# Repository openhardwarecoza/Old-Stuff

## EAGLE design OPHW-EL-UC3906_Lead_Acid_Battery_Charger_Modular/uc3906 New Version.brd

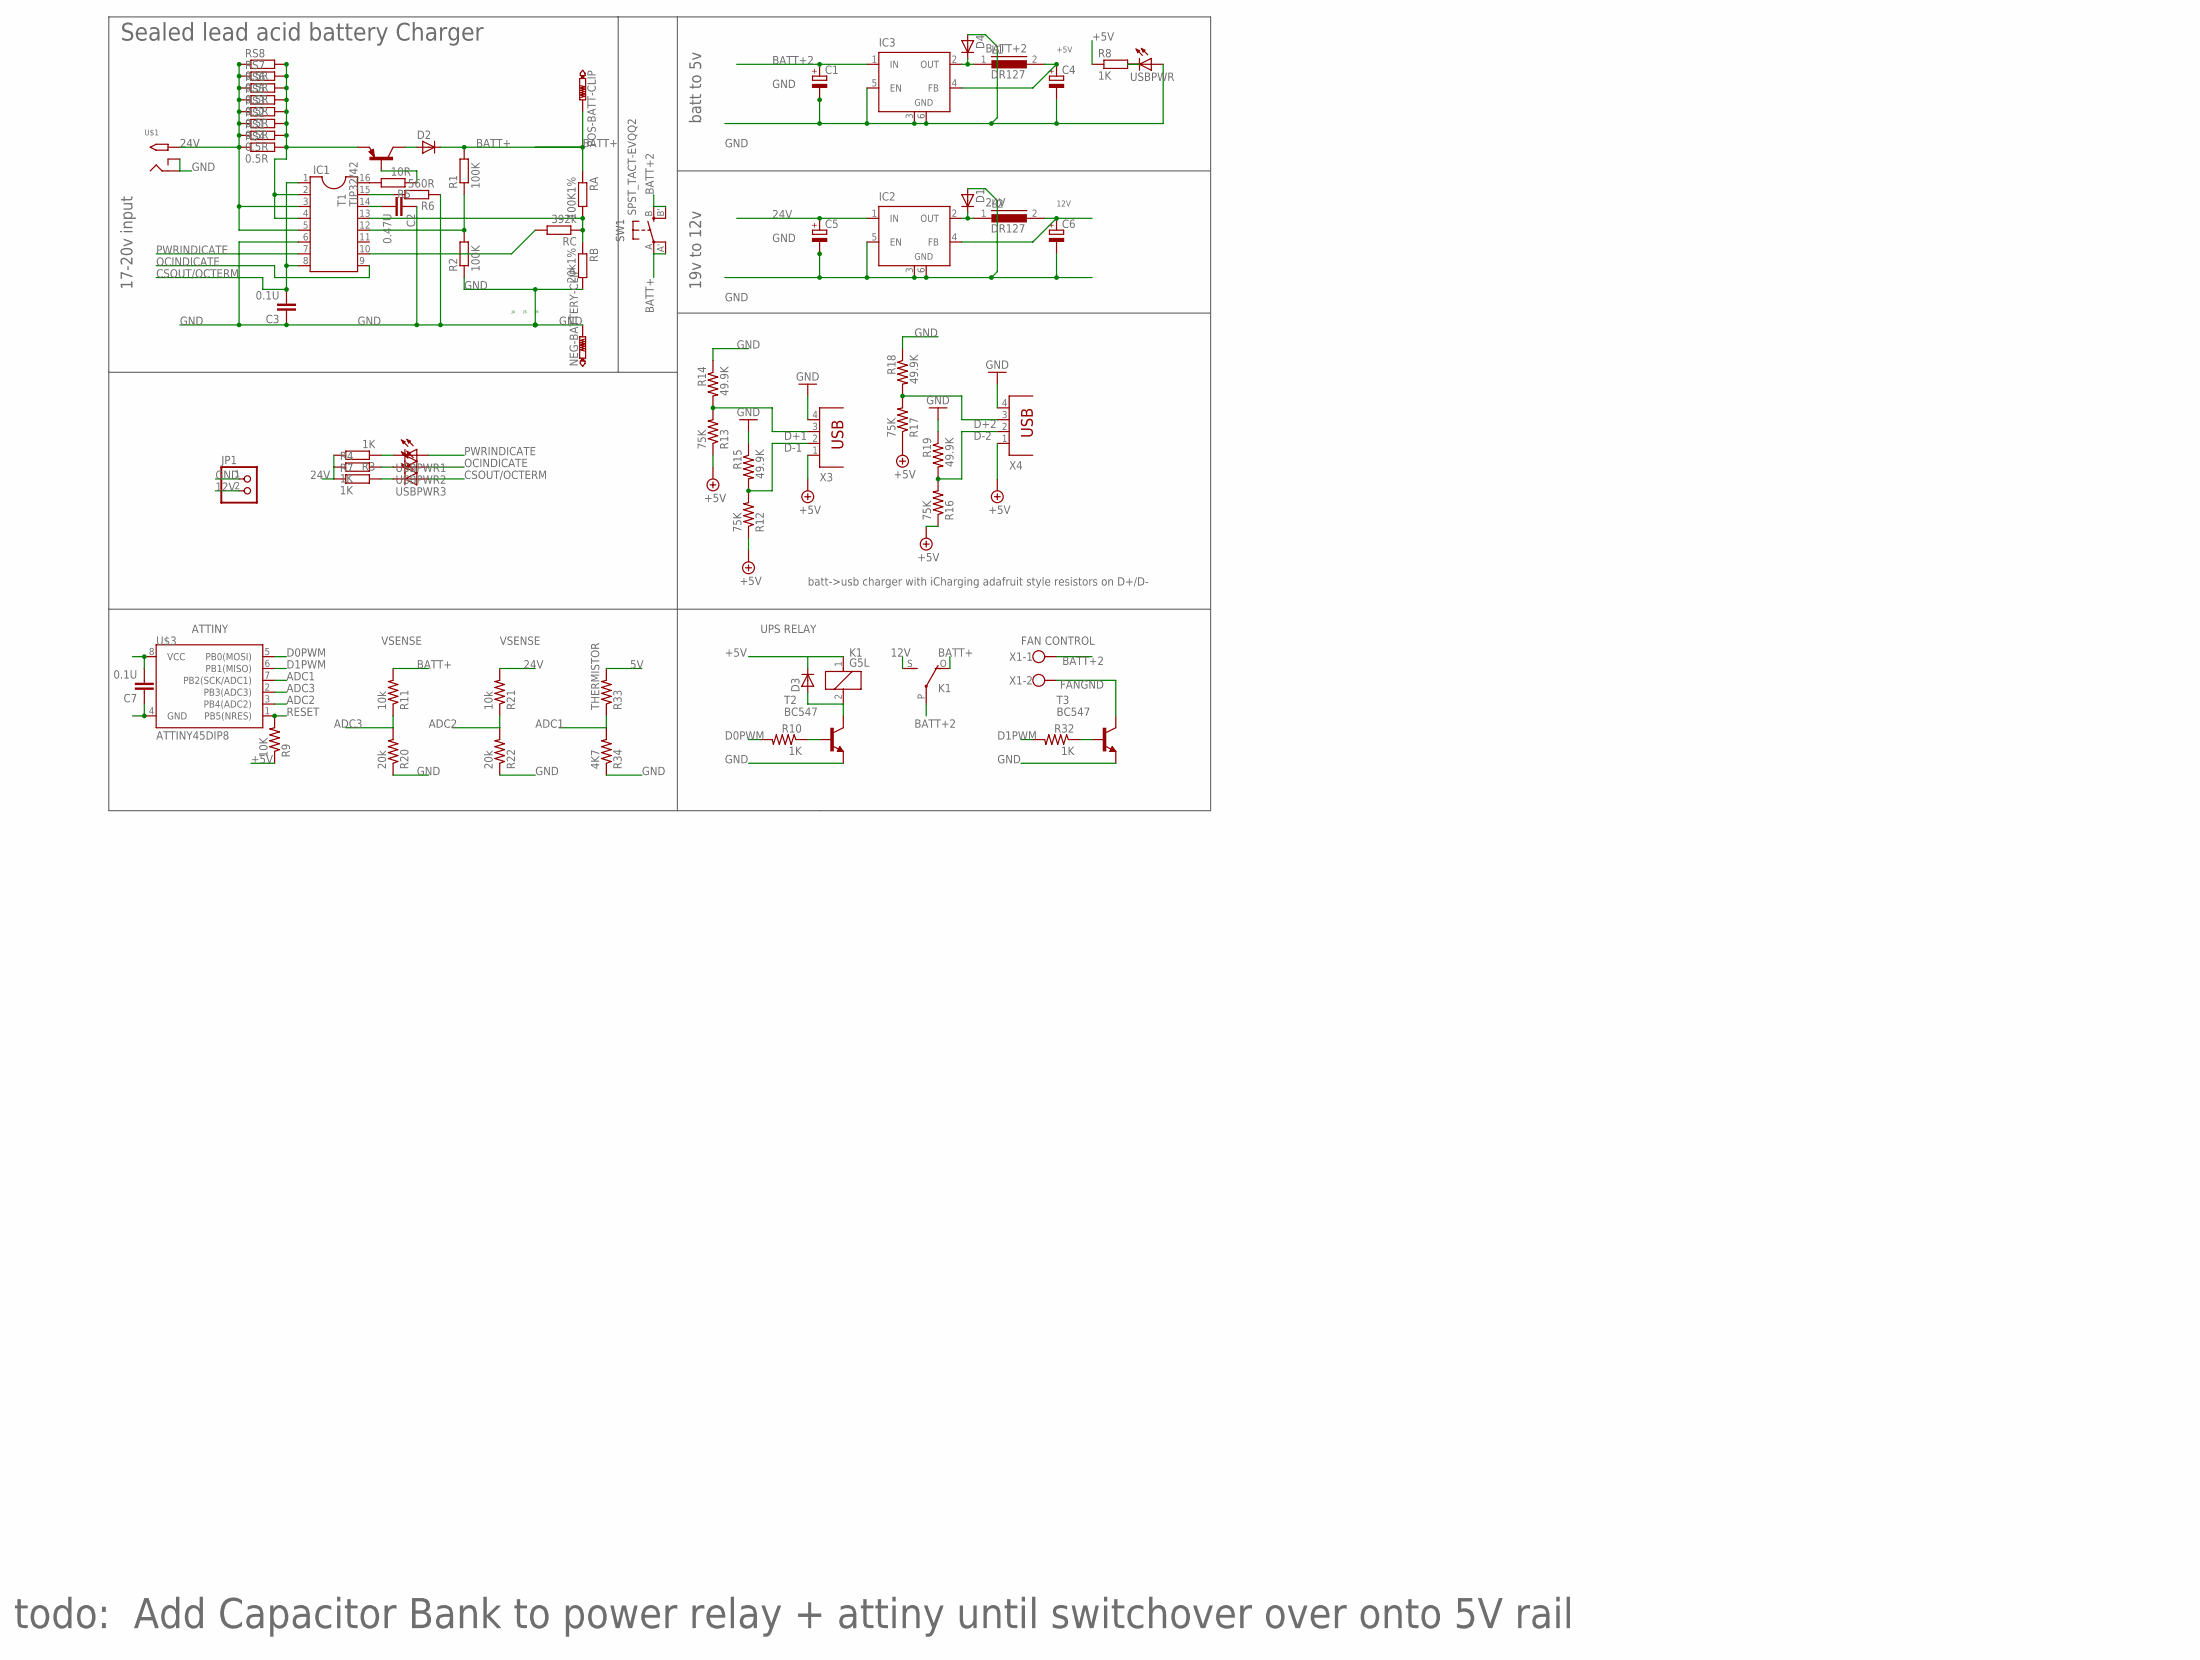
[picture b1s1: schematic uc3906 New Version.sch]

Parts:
C1, C4, C5, C6: CPOL-EUE; PANASONIC_E
C2: 0.47U; C1206
C3, C7: 0.1U; C1206
D1, D4: D-SOD-87; SOD87
D2, D3: D-MLL-41; MELF-MLL41
IC1: DIL16
IC2, IC3: LM2596S; TO263-5
JP1: PINHD-1X2; 1X02
K1: G5L; G5LE
L1, L2: DR127
NEG-BATTERY-CLIP: PTR1PAD1-20Y; P1-20Y
POS-BATT-CLIP: PTR1PAD1-20Y; P1-20Y
R1, R2: 100K; M1206
R3, R4, R7, R8, R10, R32: 1K; M1206
R5: 10R; M1206
R6: 560R; M1206
R9: 10K; M1206
R11, R21: 10k; M1206
R12, R13, R16, R17: 75K; M1206
R14, R15, R18, R19: 49.9K; M1206
R20, R22: 20k; M1206
R33: THERMISTOR; M1206
R34: 4K7; M1206
RA: 100K1%; M1206
RB: 20k1%; M1206
RC: 392k; M1206
RS1, RS2, RS3, RS4, RS5, RS6, RS7, RS8: 0.5R; R2512
SW1: SPST_TACT-EVQQ2; EVQ-Q2
T1: TIP32/42; TO220
T2, T3: BC547; TO92
U$1: 2.1MMJACKTHM; PJ-102A
U$3: ATTINY45DIP8; DIP08
USBPWR: LED3MM
USBPWR1, USBPWR2, USBPWR3: LEDCHIPLED_1206; CHIPLED_1206
X1: W237-102
X3, X4: PN87520

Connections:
5V: R33.2
12V: C6.+, IC2.4 (FB), JP1.2, K1.S, L2.2
24V: C5.+, IC1.3, IC1.5, IC2.1 (IN), R3.2, R4.1, R7.1, R21.2, RS1.1, RS2.1, RS3.1, RS4.1, RS5.1, RS6.1, RS7.1, RS8.1, U$1.TIP
+5V: C4.+, C7.2, D3.1 (C), IC3.4 (FB), K1.1, L1.2, R8.1, R9.1, R12.1, R13.1, R16.1, R17.1, U$3.8 (VCC), X3.1, X4.1
ADC1: R33.1, R34.2, U$3.7 (PB2(SCK/ADC1))
ADC2: R21.1, R22.2, U$3.3 (PB4(ADC2))
ADC3: R11.1, R20.2, U$3.2 (PB3(ADC3))
BATT+: D2.1 (C), K1.O, POS-BATT-CLIP.TP, R1.2, R11.2, RA.1, SW1.A, SW1.A' (P1)
BATT+2: C1.+, IC3.1 (IN), K1.P, SW1.B (S), SW1.B' (S1), X1.1
CHARGEENABLE: IC1.12, R1.1, R2.2
COMPENSATION: C2.2, IC1.14
CSOUT/OCTERM: C3.2, IC1.1, IC1.8, USBPWR3.A
D0PWM: R10.2, U$3.5 (PB0(MOSI))
D1PWM: R32.2, U$3.6 (PB1(MISO))
D+1: R13.2, R14.2, X3.3
D+2: R17.2, R18.2, X4.3
D-1: R12.2, R15.2, X3.2
D-2: R16.2, R19.2, X4.2
DRIVERSINK: IC1.16, R5.2
DRIVERSOURCE: IC1.15, R6.2
FANGND: T3.3 (C), X1.2
GND: C1.-, C2.1, C3.1, C4.-, C5.-, C6.-, C7.1, D1.2 (A), D4.2 (A), IC1.6, IC2.3 (GND), IC2.5 (EN), IC2.6 (GND), IC3.3 (GND), IC3.5 (EN), IC3.6 (GND), JP1.1, NEG-BATTERY-CLIP.TP, R2.1, R6.1, R14.1, R15.1, R18.1, R19.1, R20.1, R22.1, R34.1, RB.2, T2.1 (E), T3.1 (E), U$1.RING, U$1.RING_SW, U$3.4 (GND), USBPWR.A, X3.4, X4.4
IOUT: IC1.2, IC1.4, RS1.2, RS2.2, RS3.2, RS4.2, RS5.2, RS6.2, RS7.2, RS8.2, T1.3 (E)
unnamed: R3.1, USBPWR1.C
unnamed: D1.1 (C), IC2.2 (OUT), L2.1
unnamed: D4.1 (C), IC3.2 (OUT), L1.1
unnamed: R4.2, USBPWR2.C
unnamed: R7.2, USBPWR3.C
unnamed: R8.2, USBPWR.K (C)
unnamed: D3.2 (A), K1.2, T2.3 (C)
unnamed: R10.1, T2.2 (B)
unnamed: R5.1, T1.1 (B)
unnamed: D2.2 (A), T1.2 (C)
unnamed: R32.1, T3.2 (B)
OCINDICATE: IC1.9, USBPWR2.A
PWRINDICATE: IC1.7, USBPWR1.A
RESET: R9.2, U$3.1 (PB5(NRES))
STATELEVELCONTROL: IC1.10, RC.2
VSENSE: IC1.13, RA.2, RB.1, RC.1

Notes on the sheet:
batt->usb charger with iCharging adafruit style resistors on D+/D-
Sealed lead acid battery Charger
19v to 12v
batt to 5v
17-20v input
todo: Add Capacitor Bank to power relay + attiny until switchover over onto 5V rail
FAN CONTROL
UPS RELAY
VSENSE
ATTINY

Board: 2 copper layers, 69 parts (2 on the bottom side), 38 nets, no tracks yet.

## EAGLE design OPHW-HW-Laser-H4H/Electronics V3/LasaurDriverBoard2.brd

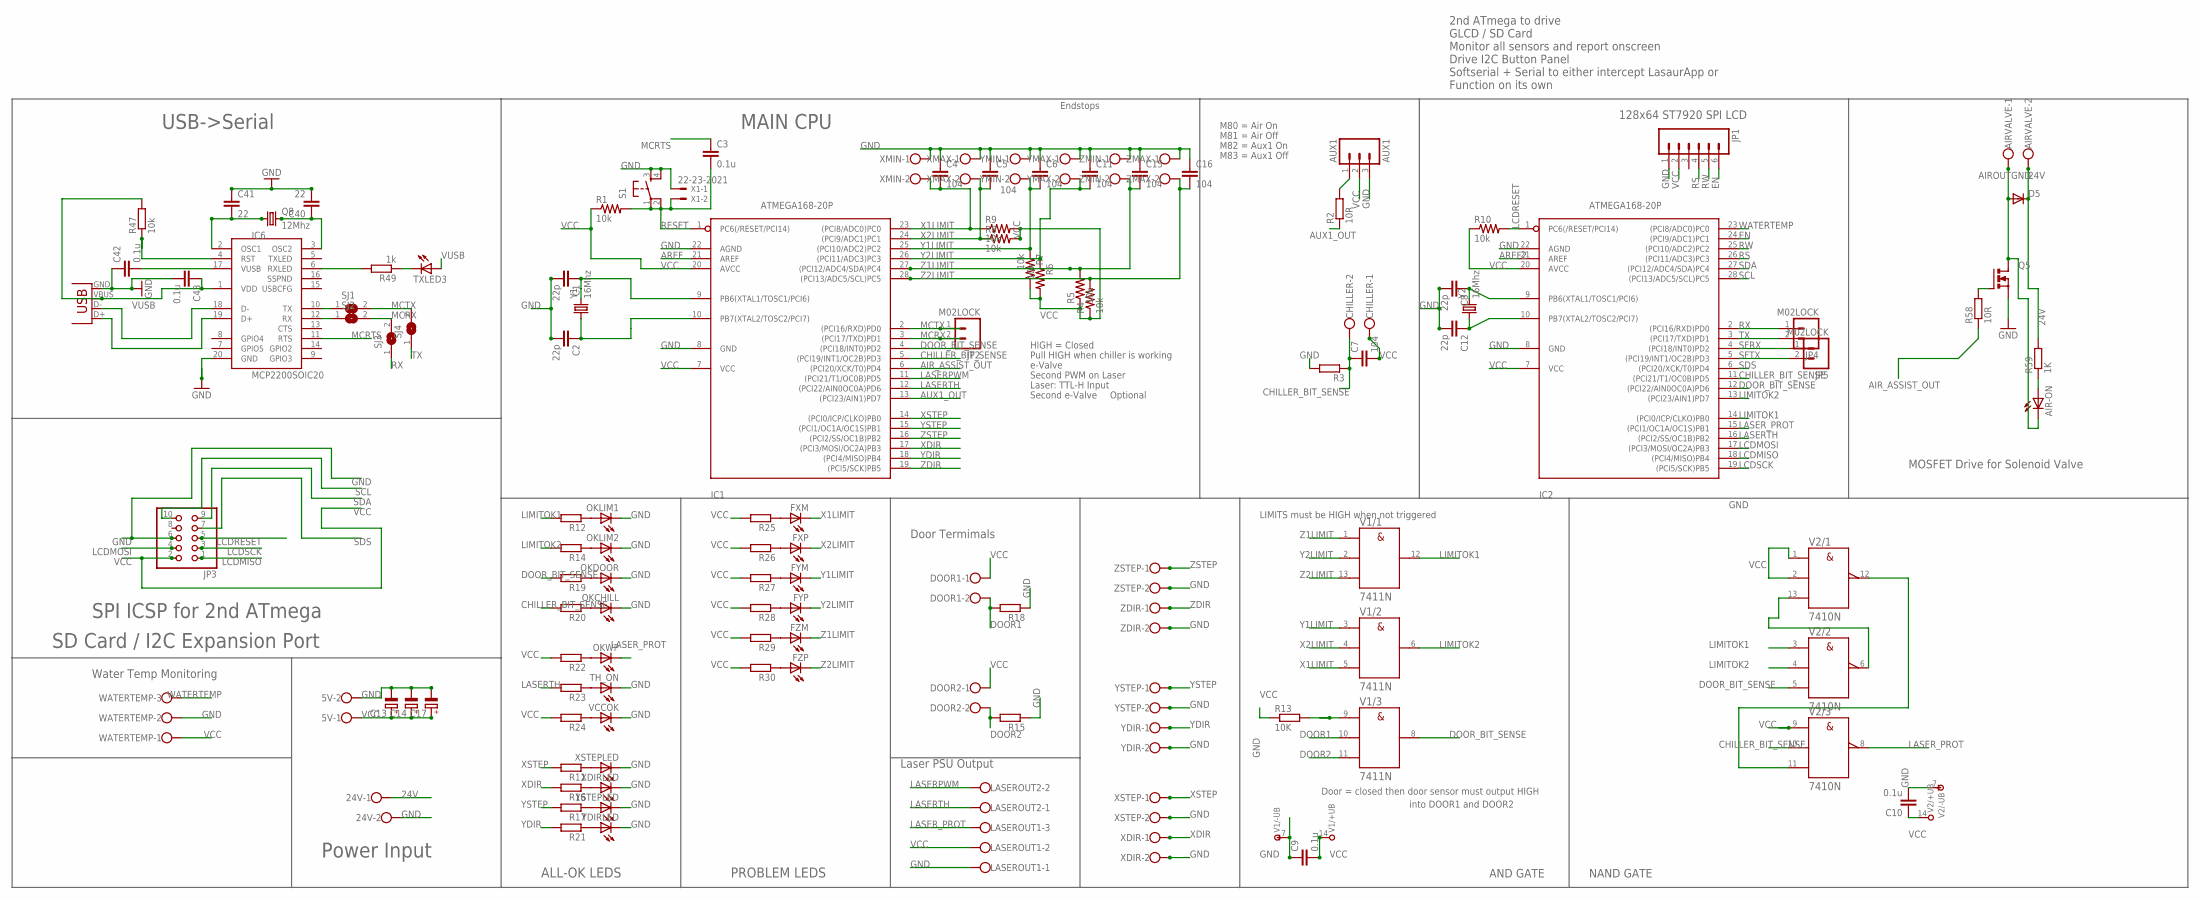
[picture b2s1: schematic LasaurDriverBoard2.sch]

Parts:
5V, 24V: W237-102
AIR-ON: LED3MM
AIRVALVE: W237-102
AUX1: AUX1; MOLEX-1X3
C1, C2, C8, C12: 22p; 1206
C3, C9, C10, C42, C43: 0.1u; 1206
C4, C6, C7, C11, C15, C16: 104; C1206
C5: C-EUC1206; C1206
C13, C14, C17: CPOL-EUB; PANASONIC_B
C40, C41: 22; 1206
CHILLER: W237-102
D5: DIODESMA-ALT; SMA-DIODE_ALT
DOOR1, DOOR2: W237-102
FXM: LED3MM
FXP: LED3MM
FYM: LED3MM
FYP: LED3MM
FZM: LED3MM
FZP: LED3MM
IC1, IC2: ATMEGA168-20P; DIL28-3
IC6: MCP2200SOIC20; SOIC20
JP1: M06LOCK; 1X06_LOCK
JP2, JP4, JP5: M02LOCK; 1X02_LOCK
JP3: PINHD-2X5; 2X05
LASEROUT1: W237-103
LASEROUT2: W237-102
OKCHILL: LED3MM
OKDOOR: LED3MM
OKLIM1, OKLIM2: LED3MM
OKWP: LED3MM
Q5: PMOSFET_NTO220BV; TO220BV
Q8: 12Mhz; HC49UP
R1, R4, R5, R6, R7, R8, R9, R10, R47: 10k; M1206
R2, R58: 10R; M1206
R3, R11, R12, R14, R15, R16, R17, R18, R19, R20, R21, R22, R23, R24, R25, R26, R27, R28, R29, R30: R-EU_M1206; M1206
R13: 10K; M1206
R49: 1k; M1206
R59: 1K; M1206
S1: TAC_SWITCHPTH; TACTILE-PTH
SJ1, SJ2, SJ3, SJ4: SJ
TH_ON: LED3MM
TXLED3: LEDSMT1206; 1206
V1: 7411N; DIL14
V2: 7410N; DIL14
VCCOK: LED3MM
WATERTEMP: W237-103
X1: 22-23-2021
X3: USB-SMD-NS; USB-MINIB-NOSTOP
XDIR: W237-102
XDIRLED: LED3MM
XMAX: W237-102
XMIN: W237-102
XSTEP: W237-102
XSTEPLED: LED3MM
Y1, Y2: 16Mhz; HC49UP
YDIR: W237-102
YDIRLED: LED3MM
YMAX: W237-102
YMIN: 104; W237-102
YSTEP: W237-102
YSTEPLED: LED3MM
ZDIR: W237-102
ZMAX: W237-102
ZMIN: W237-102
ZSTEP: W237-102

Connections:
24V: 24V.1, AIRVALVE.2, D5.C, R59.2
AIROUTGND: AIR-ON.K (C), AIRVALVE.1, D5.A, Q5.D
AIR_ASSIST_OUT: IC1.6 ((PCI20/XCK/T0)PD4), R58.1
AREF: IC1.21 (AREF)
AREF2: IC2.21 (AREF)
AUX1_OUT: IC1.13 ((PCI23/AIN1)PD7), R2.1
CHILLER_BIT_SENSE: C7.1, CHILLER.2, IC1.5 ((PCI19/INT1/OC2B)PD3), IC2.11 ((PCI21/T1/OC0B)PD5), R3.1, R20.2, V2.10 (B)
DOOR1: DOOR1.2, R18.2, V1.10 (B)
DOOR2: DOOR2.2, R15.2, V1.11 (C)
DOOR_BIT_SENSE: IC1.4 ((PCI18/INT0)PD2), IC2.12 ((PCI22/AIN0OC0A)PD6), R19.2, V1.8 (Y), V2.5 (C)
EN: IC2.24 ((PCI9/ADC1)PC1), JP1.6
GND: 5V.2, 24V.2, AUX1.3, C1.2, C2.2, C4.1, C5.1, C6.1, C8.2, C9.1, C10.2, C11.1, C12.2, C13.-, C14.-, C15.1, C16.1, C17.-, C40.2, C41.1, C42.1, C43.2, IC1.8 (GND), IC1.22 (AGND), IC2.8 (GND), IC2.22 (AGND), IC6.20 (GND), JP1.1, JP3.6, LASEROUT1.1, OKCHILL.K (C), OKDOOR.K (C), OKLIM1.K (C), OKLIM2.K (C), Q5.S, R3.2, R15.1, R18.1, S1.3, S1.4, TH_ON.K (C), V1.7 (-UB), V2.7 (-UB), VCCOK.K (C), WATERTEMP.2, X1.1, X3.GND, XDIR.2, XDIRLED.K (C), XMAX.1, XMIN.1, XSTEP.2, XSTEPLED.K (C), YDIR.2, YDIRLED.K (C), YMAX.1, YMIN.1, YSTEP.2, YSTEPLED.K (C), ZDIR.2, ZMAX.1, ZMIN.1, ZSTEP.2
LASERPWM: IC1.11 ((PCI21/T1/OC0B)PD5), LASEROUT2.2
LASERTH: IC1.12 ((PCI22/AIN0OC0A)PD6), IC2.16 ((PCI2/SS/OC1B)PB2), LASEROUT2.1, R23.2
LASER_PROT: IC2.15 ((PCI1/OC1A/OC1S)PB1), LASEROUT1.3, OKWP.K (C), V2.8 (Y)
LCDMISO: IC2.18 ((PCI4/MISO)PB4), JP3.1
LCDMOSI: IC2.17 ((PCI3/MOSI/OC2A)PB3), JP3.4
LCDRESET: IC2.1 (PC6(/RESET/PCI14)), JP3.5, R10.2
LCDSCK: IC2.19 ((PCI5/SCK)PB5), JP3.3
LIMITOK1: IC2.14 ((PCI0/ICP/CLKO)PB0), R12.2, V1.12 (Y), V2.3 (A)
LIMITOK2: IC2.13 ((PCI23/AIN1)PD7), R14.2, V1.6 (Y), V2.4 (B)
MCRTS: C3.1, IC6.11 (RTS)
MCRX: IC1.3 ((PCI17/TXD)PD1), JP2.2, SJ2.2, SJ3.2
MCRXPRE: IC6.12 (RX), SJ2.1
MCTX: IC1.2 ((PCI16/RXD)PD0), JP2.1, SJ1.2, SJ4.2
MXTCPRE: IC6.10 (TX), SJ1.1
unnamed: R11.1, XSTEPLED.A
unnamed: R16.1, XDIRLED.A
unnamed: AUX1.1, R2.2
unnamed: V2.6 (Y), V2.13 (C)
unnamed: OKLIM1.A, R12.1
unnamed: R17.1, YSTEPLED.A
unnamed: R21.1, YDIRLED.A
unnamed: R13.2, V1.9 (A)
unnamed: OKLIM2.A, R14.1
unnamed: OKDOOR.A, R19.1
unnamed: OKCHILL.A, R20.1
unnamed: OKWP.A, R22.1
unnamed: R23.1, TH_ON.A
unnamed: R24.1, VCCOK.A
unnamed: FXM.A, R25.1
unnamed: FXP.A, R26.1
unnamed: FYM.A, R27.1
unnamed: FYP.A, R28.1
unnamed: FZM.A, R29.1
unnamed: FZP.A, R30.1
unnamed: Q5.G, R58.2
unnamed: AIR-ON.A, R59.1
unnamed: C41.2, IC6.2 (OSC1), Q8.1
unnamed: C40.1, IC6.3 (OSC2), Q8.2
unnamed: IC6.18 (D-), X3.D-
unnamed: IC6.19 (D+), X3.D+
unnamed: C42.2, IC6.17 (VUSB)
unnamed: IC6.4 (RST), R47.1
unnamed: IC6.6 (RXLED), R49.2
unnamed: R49.1, TXLED3.C
NANDOK: V2.11 (C), V2.12 (Y)
RESET: C3.2, IC1.1 (PC6(/RESET/PCI14)), R1.2, S1.1, S1.2, X1.2
RS: IC2.26 ((PCI11/ADC3)PC3), JP1.4
RW: IC2.25 ((PCI10/ADC2)PC2), JP1.5
RX: IC2.2 ((PCI16/RXD)PD0), JP4.1, SJ3.1
SCL: IC2.28 ((PCI13/ADC5/SCL)PC5), JP3.10
SDA: IC2.27 ((PCI12/ADC4/SDA)PC4), JP3.9
SDS: IC2.6 ((PCI20/XCK/T0)PD4), JP3.7
SFRX: IC2.4 ((PCI18/INT0)PD2), JP5.1
SFTX: IC2.5 ((PCI19/INT1/OC2B)PD3), JP5.2
TX: IC2.3 ((PCI17/TXD)PD1), JP4.2, SJ4.1
VCC: 5V.1, AUX1.2, C7.2, C9.2, C10.1, C13.+, C14.+, C17.+, CHILLER.1, DOOR1.1, DOOR2.1, IC1.7 (VCC), IC1.20 (AVCC), IC2.7 (VCC), IC2.20 (AVCC), JP1.2, JP3.2, LASEROUT1.2, R1.1, R4.1, R5.1, R6.2, R7.2, R8.2, R9.2, R10.1, R13.1, R22.2, R24.2, R25.2, R26.2, R27.2, R28.2, R29.2, R30.2, V1.14 (+UB), V2.1 (A), V2.2 (B), V2.9 (A), V2.14 (+UB), WATERTEMP.1
VUSB: C43.1, IC6.1 (VDD), R47.2, TXLED3.A, X3.VBUS
WATERTEMP: IC2.23 ((PCI8/ADC0)PC0), WATERTEMP.3
X1LIMIT: C4.2, FXM.K (C), IC1.23 ((PCI8/ADC0)PC0), R9.1, V1.5 (C), XMIN.2
X2LIMIT: C5.2, FXP.K (C), IC1.24 ((PCI9/ADC1)PC1), R8.1, V1.4 (B), XMAX.2
XDIR: IC1.17 ((PCI3/MOSI/OC2A)PB3), R16.2, XDIR.1
XSTEP: IC1.14 ((PCI0/ICP/CLKO)PB0), R11.2, XSTEP.1
XTAL1: C1.1, IC1.9 (PB6(XTAL1/TOSC1/PCI6)), Y1.2
XTAL2: C2.1, IC1.10 (PB7(XTAL2/TOSC2/PCI7)), Y1.1
XTAL3: C12.1, IC2.10 (PB7(XTAL2/TOSC2/PCI7)), Y2.1
XTAL4: C8.1, IC2.9 (PB6(XTAL1/TOSC1/PCI6)), Y2.2
Y1LIMIT: C6.2, FYM.K (C), IC1.25 ((PCI10/ADC2)PC2), R7.1, V1.3 (A), YMIN.2
Y2LIMIT: C11.2, FYP.K (C), IC1.26 ((PCI11/ADC3)PC3), R6.1, V1.2 (B), YMAX.2
YDIR: IC1.18 ((PCI4/MISO)PB4), R21.2, YDIR.1
YSTEP: IC1.15 ((PCI1/OC1A/OC1S)PB1), R17.2, YSTEP.1
Z1LIMIT: C15.2, FZM.K (C), IC1.27 ((PCI12/ADC4/SDA)PC4), R5.2, V1.1 (A), ZMIN.2
Z2LIMIT: C16.2, FZP.K (C), IC1.28 ((PCI13/ADC5/SCL)PC5), R4.2, V1.13 (C), ZMAX.2
ZDIR: IC1.19 ((PCI5/SCK)PB5), ZDIR.1
ZSTEP: IC1.16 ((PCI2/SS/OC1B)PB2), ZSTEP.1

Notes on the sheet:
MAIN CPU
M80 = Air On
M81 = Air Off
M82 = Aux1 On
M83 = Aux1 Off
Second PWM on Laser
HIGH = Closed
e-Valve
Second e-Valve
Pull HIGH when chiller is working
Laser: TTL-H Input
Optional
Endstops
Door = closed then door sensor must output HIGH
into DOOR1 and DOOR2
LIMITS must be HIGH when not triggered
PROBLEM LEDS
ALL-OK LEDS
USB->Serial
SPI ICSP for 2nd ATmega
SD Card / I2C Expansion Port
Power Input
Door Termimals
Laser PSU Output
Water Temp Monitoring
AND GATE
NAND GATE
MOSFET Drive for Solenoid Valve
2nd ATmega to drive GLCD / SD Card Monitor all sensors and report onscreen Drive I2C Button Panel Softserial + Serial to either intercept LasaurApp or Function on its own
128x64 ST7920 SPI LCD

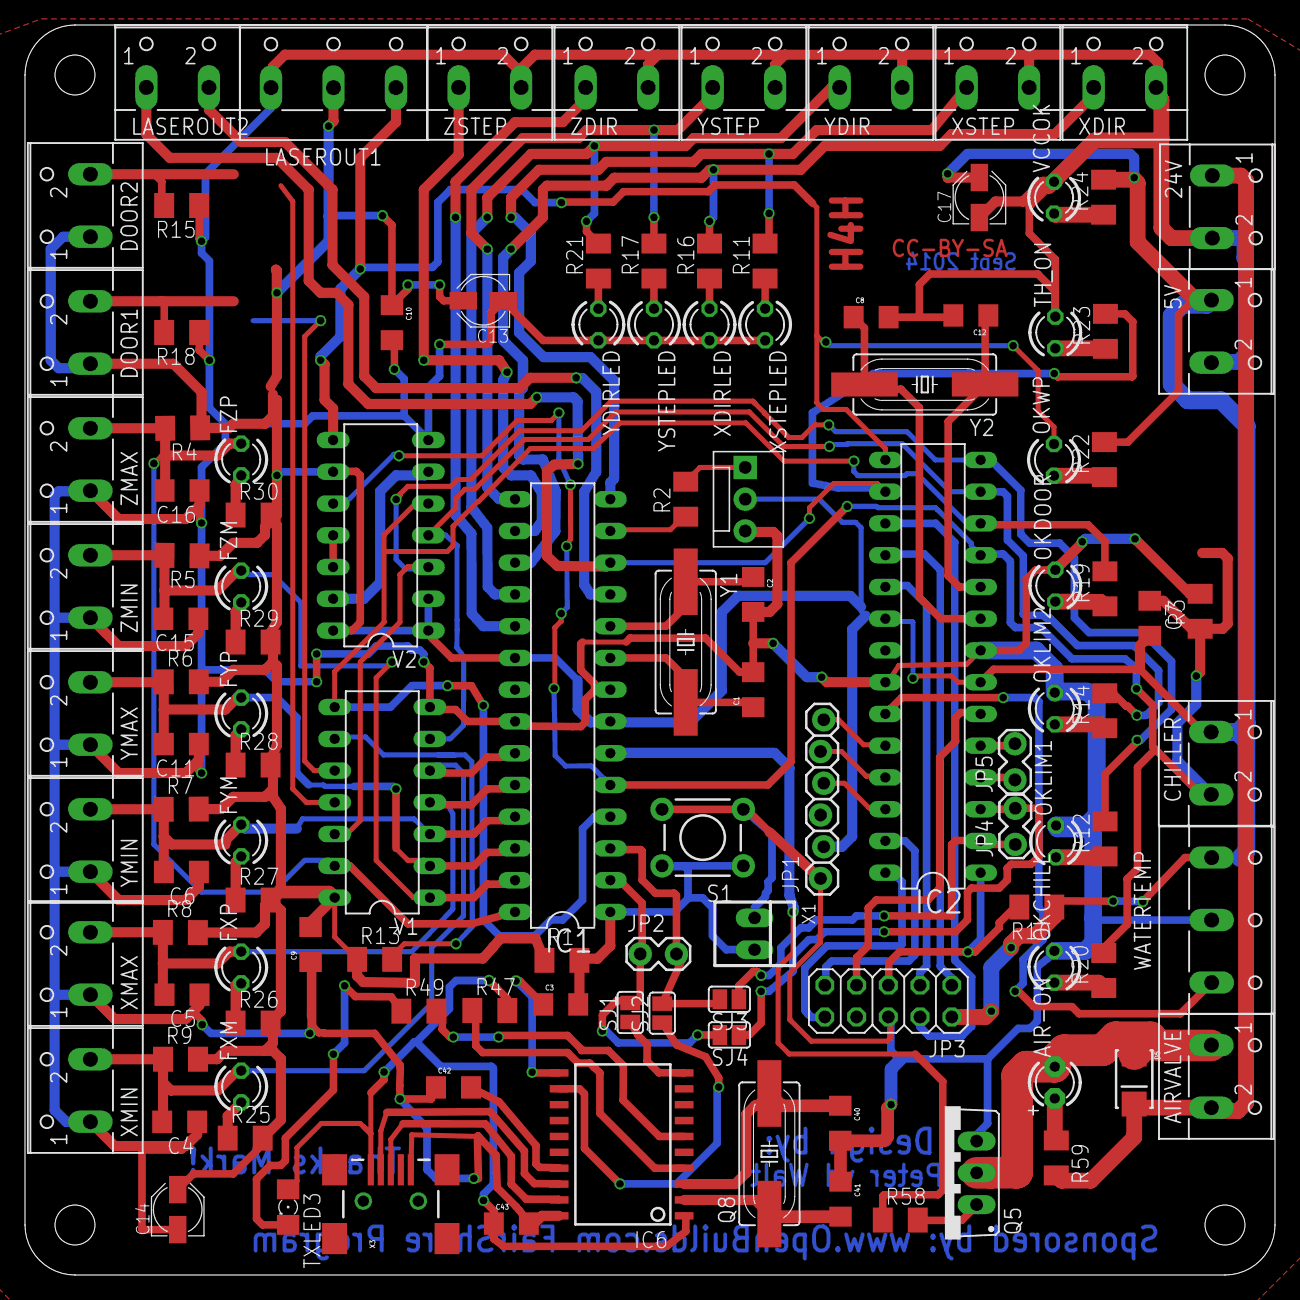
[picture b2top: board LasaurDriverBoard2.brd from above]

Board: 2 copper layers, 100.0 x 100.0 mm, 120 parts (0 on the bottom side), 84 nets.

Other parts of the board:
U$2: DP100100_V1
U$6: LOGO

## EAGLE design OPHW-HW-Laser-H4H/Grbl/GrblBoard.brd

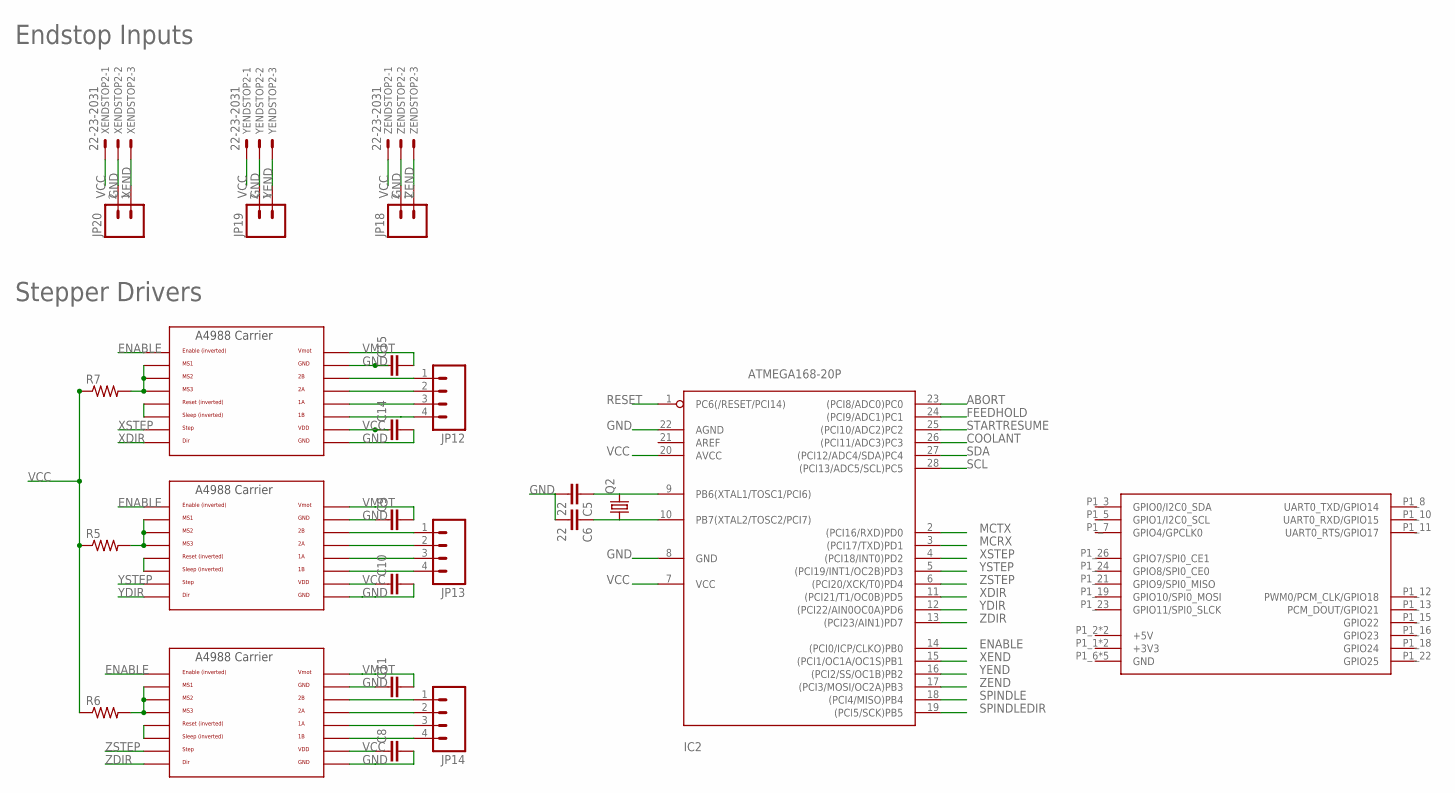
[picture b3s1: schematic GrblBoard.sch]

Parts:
C5, C6: 22; 1206
C8, C9, C10, C11, C14, C15: CAP1206; 1206
IC2: ATMEGA168-20P; DIL28-3
JP12, JP13, JP14: M04SCREW; SCREWTERMINAL-3.5MM-4
JP18, JP19, JP20: M023.5MM; SCREWTERMINAL-3.5MM-2
Q2: CRYSTALHC49UP; HC49UP
R5, R6, R7: RESISTOR1206; 1206
U$1: RPI-B-V1SHIELD; RPI-B-V1-SHIELD
XENDSTOP2: 22-23-2031
XPOL: POLOLU_A4983CARRIER; A4988BREAKOUT
YENDSTOP2: 22-23-2031
YPOL: POLOLU_A4983CARRIER; A4988BREAKOUT
ZENDSTOP2: 22-23-2031
ZPOL: POLOLU_A4983CARRIER; A4988BREAKOUT

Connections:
+3V3: U$1.P1_1 (+3V3), U$1.P1_17 (+3V3)
+5V: U$1.P1_2 (+5V), U$1.P1_4 (+5V)
ABORT: IC2.23 ((PCI8/ADC0)PC0)
COOLANT: IC2.26 ((PCI11/ADC3)PC3)
ENABLE: IC2.14 ((PCI0/ICP/CLKO)PB0), XPOL.EN, YPOL.EN, ZPOL.EN
FEEDHOLD: IC2.24 ((PCI9/ADC1)PC1)
GND: C5.2, C6.2, C8.2, C9.1, C10.2, C11.1, C14.2, C15.1, IC2.8 (GND), IC2.22 (AGND), JP18.2, JP19.2, JP20.2, U$1.P1_6 (GND), U$1.P1_9 (GND), U$1.P1_14 (GND), U$1.P1_20 (GND), U$1.P1_25 (GND), XENDSTOP2.2, XPOL.GND, XPOL.GND@0 (GND), YENDSTOP2.2, YPOL.GND, YPOL.GND@0 (GND), ZENDSTOP2.2, ZPOL.GND, ZPOL.GND@0 (GND)
MCRX: IC2.3 ((PCI17/TXD)PD1)
MCTX: IC2.2 ((PCI16/RXD)PD0)
unnamed: ZPOL.RST, ZPOL.SLP (SLEEP)
unnamed: YPOL.RST, YPOL.SLP (SLEEP)
unnamed: XPOL.RST, XPOL.SLP (SLEEP)
unnamed: R7.2, XPOL.MS1, XPOL.MS2, XPOL.MS3
unnamed: R5.2, YPOL.MS1, YPOL.MS2, YPOL.MS3
unnamed: R6.2, ZPOL.MS1, ZPOL.MS2, ZPOL.MS3
unnamed: JP14.4, ZPOL.1B
unnamed: JP14.3, ZPOL.1A
unnamed: JP14.2, ZPOL.2A
unnamed: JP14.1, ZPOL.2B
unnamed: JP13.1, YPOL.2B
unnamed: JP13.2, YPOL.2A
unnamed: JP13.3, YPOL.1A
unnamed: JP13.4, YPOL.1B
unnamed: JP12.4, XPOL.1B
unnamed: JP12.3, XPOL.1A
unnamed: JP12.2, XPOL.2A
unnamed: JP12.1, XPOL.2B
RESET: IC2.1 (PC6(/RESET/PCI14))
SCL: IC2.28 ((PCI13/ADC5/SCL)PC5)
SDA: IC2.27 ((PCI12/ADC4/SDA)PC4)
SPINDLE: IC2.18 ((PCI4/MISO)PB4)
SPINDLEDIR: IC2.19 ((PCI5/SCK)PB5)
STARTRESUME: IC2.25 ((PCI10/ADC2)PC2)
VCC: C8.1, C10.1, C14.1, IC2.7 (VCC), IC2.20 (AVCC), R5.1, R6.1, R7.1, XENDSTOP2.1, XPOL.VDD, YENDSTOP2.1, YPOL.VDD, ZENDSTOP2.1, ZPOL.VDD
VMOT: C9.2, C11.2, C15.2, XPOL.VMOT, YPOL.VMOT, ZPOL.VMOT
XDIR: IC2.11 ((PCI21/T1/OC0B)PD5), XPOL.DIR
XEND: IC2.15 ((PCI1/OC1A/OC1S)PB1), JP20.1, XENDSTOP2.3
XSTEP: IC2.4 ((PCI18/INT0)PD2), XPOL.STEP
XTAL1: C5.1, IC2.9 (PB6(XTAL1/TOSC1/PCI6)), Q2.2
XTAL2: C6.1, IC2.10 (PB7(XTAL2/TOSC2/PCI7)), Q2.1
YDIR: IC2.12 ((PCI22/AIN0OC0A)PD6), YPOL.DIR
YEND: IC2.16 ((PCI2/SS/OC1B)PB2), JP19.1, YENDSTOP2.3
YSTEP: IC2.5 ((PCI19/INT1/OC2B)PD3), YPOL.STEP
ZDIR: IC2.13 ((PCI23/AIN1)PD7), ZPOL.DIR
ZEND: IC2.17 ((PCI3/MOSI/OC2A)PB3), JP18.1, ZENDSTOP2.3
ZSTEP: IC2.6 ((PCI20/XCK/T0)PD4), ZPOL.STEP

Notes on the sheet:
Endstop Inputs
Stepper Drivers

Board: 2 copper layers, 26 parts (0 on the bottom side), 35 nets, no tracks yet.

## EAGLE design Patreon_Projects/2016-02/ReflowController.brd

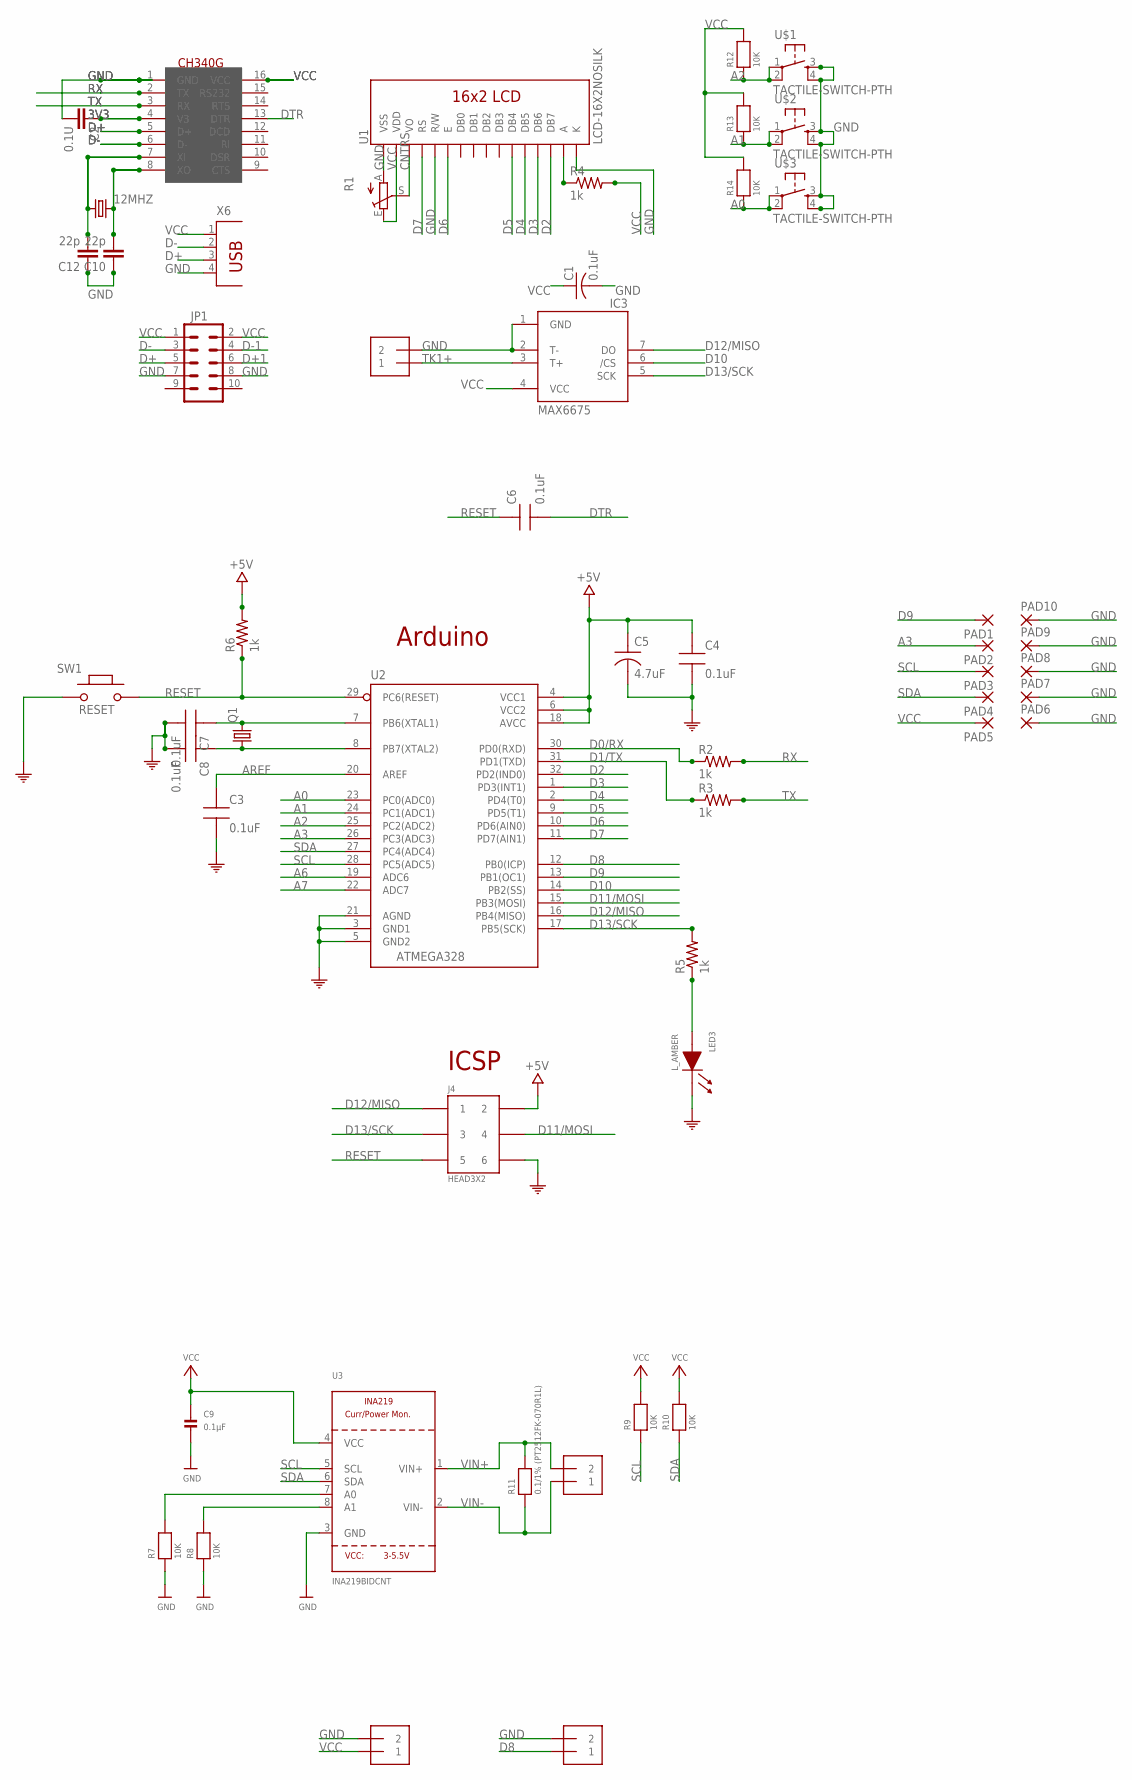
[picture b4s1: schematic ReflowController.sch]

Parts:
12MHZ: CRYSTALHC49UP; HC49UP
C1: 0.1uF; C0805K
C2: 0.1U; C1206
C3, C4, C6, C7, C8: 0.1uF; CAP0805-NP
C5: 4.7uF; TAN-A
C9: 0.1µF; 0805
C10, C12: 22p; C1206
IC3: MAX6675; SO08
J1, J3, J5: TERMBLOCK_1X2-3.5MM; 1X2-3.5MM
J2: 1X2-3.5MM
J4: HEAD3X2
JP1: M05X2SHD_LOCK; 2X5-SHROUDED_LOCK
LED3: L_AMBER; LED0805
PAD1, PAD2, PAD3, PAD4, PAD5, PAD6, PAD7, PAD8, PAD9, PAD10: SMD2; SMD1,27-2,54
Q1: CRYSTALHC49UP; HC49UP
R1: TRIM_EU-CA9V; CA9V
R2, R3, R4, R5, R6: 1k; 1206
R7, R8, R9, R10, R12, R13, R14: 10K; 0805
R11: 0.1/1% (PT2512FK-070R1L); 2512
SW1: RESET; 157SW
U1: LCD-16X2NOSILK; LCD-16X2_NOSILK
U2: ATMEGA328; QFP032
U3: INA219BIDCNT; SOT23-8
U$1, U$2, U$3: TACTILE-SWITCH-PTH; TAC-SWITCH-PTH
U$4: CH340G; SOIC16
X6: PN61729

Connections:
3V3: C2.1, U$4.4 (V3)
A0: R14.1, U2.23 (PC0(ADC0)), U$3.1, U$3.2
A1: R13.1, U2.24 (PC1(ADC1)), U$2.1, U$2.2
A2: R12.1, U2.25 (PC2(ADC2)), U$1.1, U$1.2
A3: PAD2.1, U2.26 (PC3(ADC3))
A6: U2.19 (ADC6)
A7: U2.22 (ADC7)
AREF: C3.1, U2.20 (AREF)
CNTRS: R1.S, U1.3 (VO)
D0/RX: R2.1, U2.30 (PD0(RXD))
D1/TX: R3.1, U2.31 (PD1(TXD))
D2: U1.14 (DB7), U2.32 (PD2(IND0))
D3: U1.13 (DB6), U2.1 (PD3(INT1))
D4: U1.12 (DB5), U2.2 (PD4(T0))
D5: U1.11 (DB4), U2.9 (PD5(T1))
D6: U1.6 (E), U2.10 (PD6(AIN0))
D7: U1.4 (RS), U2.11 (PD7(AIN1))
D8: J3.1, U2.12 (PB0(ICP))
D9: PAD1.1, U2.13 (PB1(OC1))
D10: IC3.6 (/CS), U2.14 (PB2(SS))
D11/MOSI: J4.4, U2.15 (PB3(MOSI))
D12/MISO: IC3.7 (DO), J4.1, U2.16 (PB4(MISO))
D13/SCK: IC3.5 (SCK), J4.3, R5.2, U2.17 (PB5(SCK))
D+: JP1.5, U$4.5 (D+), X6.3
D+1: JP1.6
D-: JP1.3, U$4.6 (D-), X6.2
D-1: JP1.4
DTR: C6.2, U$4.13 (DTR)
GND: C1.2, C2.2, C3.2, C4.2, C5.2, C7.2, C8.2, C9.2, C10.1, C12.1, IC3.1 (GND), IC3.2 (T-), J2.2, J3.2, J4.6, J5.2, JP1.7, JP1.8, LED3.1 (CA), PAD6.1, PAD7.1, PAD8.1, PAD9.1, PAD10.1, R1.A, R7.1, R8.1, SW1.1, U1.1 (VSS), U1.5 (R/W), U1.16 (K), U2.3 (GND1), U2.5 (GND2), U2.21 (AGND), U3.3 (GND), U$1.3, U$1.4, U$2.3, U$2.4, U$3.3, U$3.4, U$4.1 (GND), X6.4
unnamed: C8.1, Q1.1, U2.8 (PB7(XTAL2))
unnamed: C7.1, Q1.2, U2.7 (PB6(XTAL1))
unnamed: R8.2, U3.8 (A1)
unnamed: R7.2, U3.7 (A0)
unnamed: LED3.2 (AN), R5.1
unnamed: R4.1, U1.15 (A)
unnamed: 12MHZ.1, C12.2, U$4.7 (XI)
unnamed: 12MHZ.2, C10.2, U$4.8 (XO)
RESET: C6.1, J4.5, R6.1, SW1.2, U2.29 (PC6(RESET))
RX: R2.2, U$4.2 (TX)
SCL: PAD3.1, R9.1, U2.28 (PC5(ADC5)), U3.5 (SCL)
SDA: PAD4.1, R10.1, U2.27 (PC4(ADC4)), U3.6 (SDA)
TK1+: IC3.3 (T+), J2.1
TX: R3.2, U$4.3 (RX)
VCC: C1.1, C4.1, C5.1, C9.1, IC3.4 (VCC), J4.2, J5.1, JP1.1, JP1.2, PAD5.1, R1.E, R4.2, R6.2, R9.2, R10.2, R12.2, R13.2, R14.2, U1.2 (VDD), U2.4 (VCC1), U2.6 (VCC2), U2.18 (AVCC), U3.4 (VCC), U$4.16 (VCC), X6.1
VIN+: J1.2, R11.2, U3.1 (VIN+)
VIN-: J1.1, R11.1, U3.2 (VIN-)

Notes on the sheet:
Arduino
ICSP

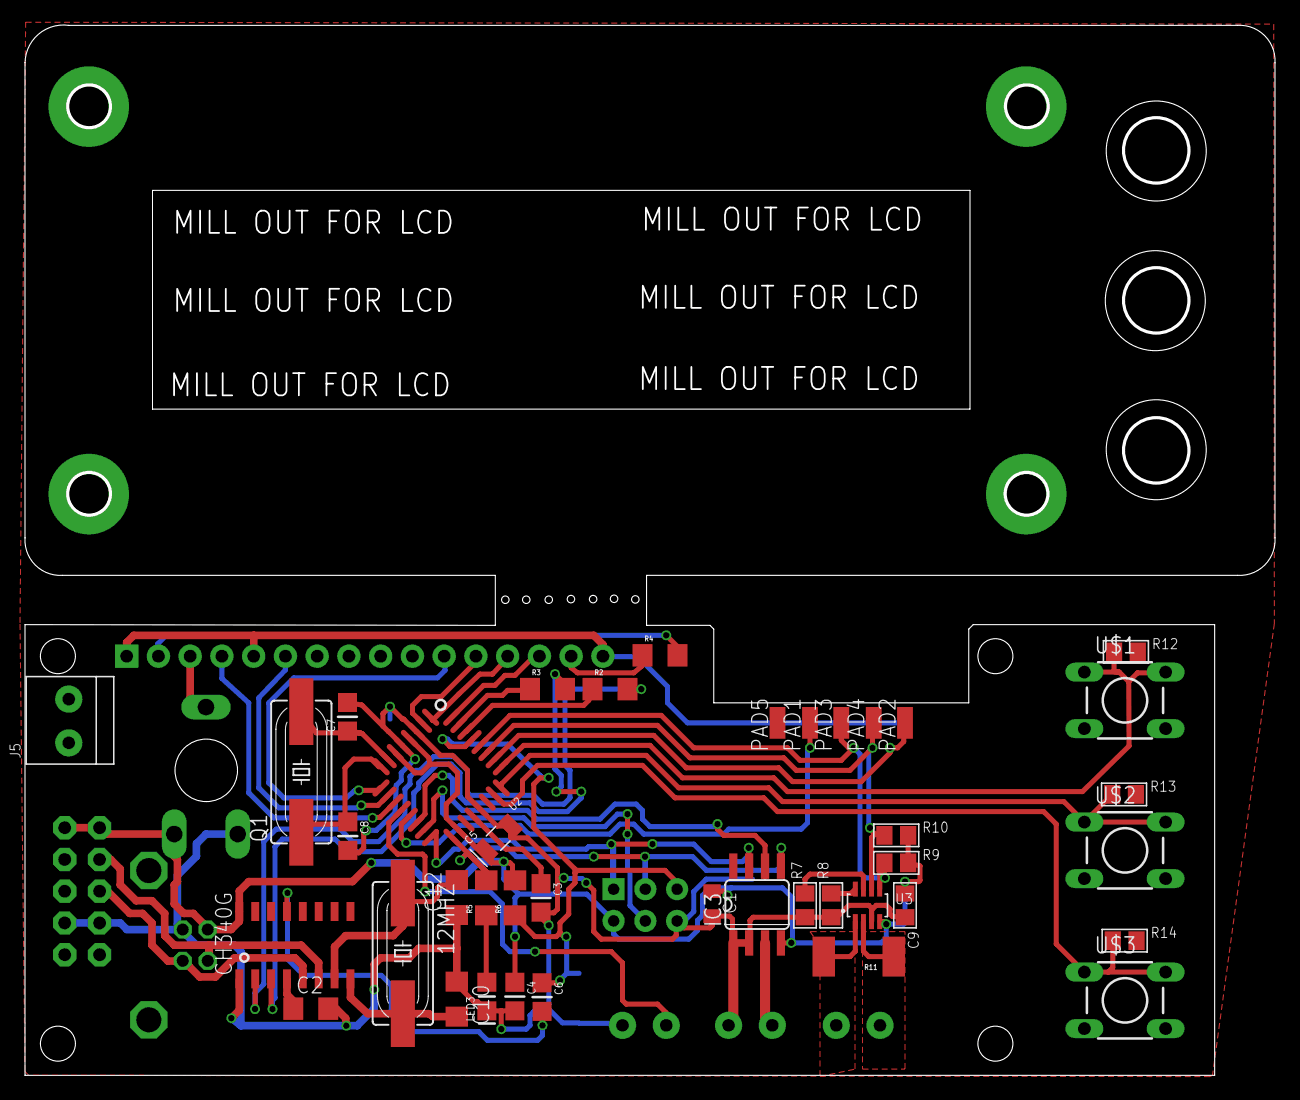
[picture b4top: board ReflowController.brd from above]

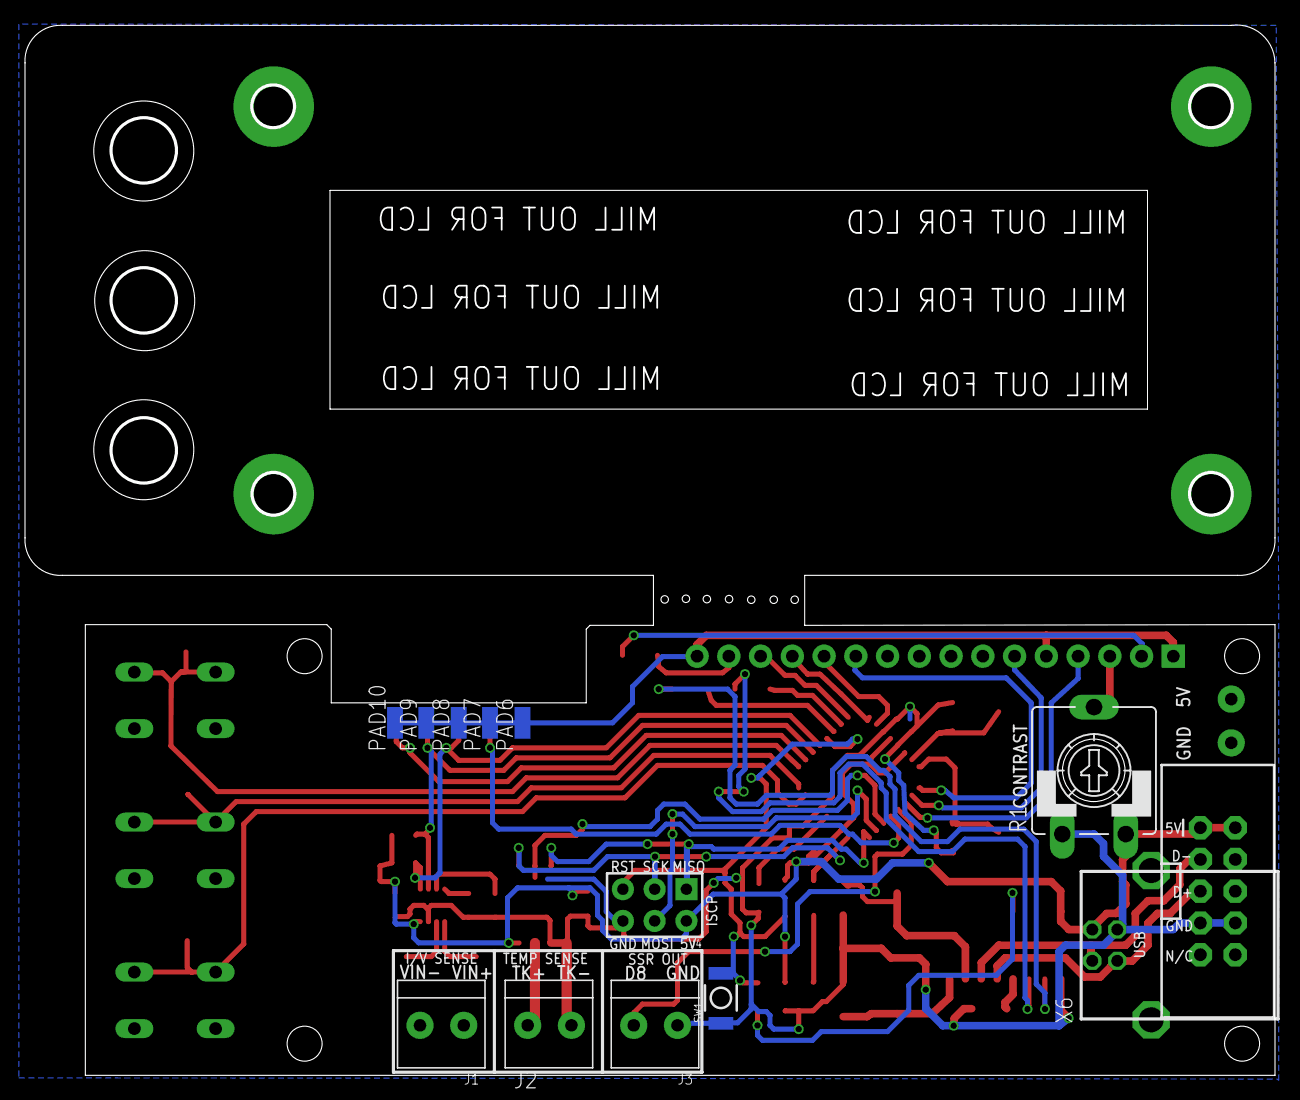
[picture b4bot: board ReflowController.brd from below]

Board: 2 copper layers, 100.0 x 84.0 mm, 54 parts (13 on the bottom side), 42 nets.

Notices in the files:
OPHW-HW-Laser-H4H/Electronics V3/LasaurDriverBoard2.brd:
CC-BY-SA
parts and their libraries:
SparkFun-Passives: Licensing: CC v3.0 Share-Alike You are welcome to use this library for commercial purposes.
raspberry: This library stands under the CERN Open Hardware Licence.
GeekAmmo: Licensing:Creative Commons ShareAlike 4.0 International - https://creativecommons.org/licenses/by-sa/4.0
